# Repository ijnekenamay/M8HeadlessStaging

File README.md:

# M8 Headless Staging

This is a DIY project to push the [Dirtywave M8 Headless](https://github.com/Dirtywave/M8HeadlessFirmware) into a PCB and make it handheld.
Test build was done on the fabricated PCB. MIDI I/O AUDIO OUT seems to be working well.
Kicad data has been withheld from the public due to criticism that it would damage the market. Please contact.

## Now progress

- [x] Idea sketch
- [x] Draw proto Schematics
- [x] Design proto PCB
- [x] Proto type
- [x] Design PCB
- [x] Fabrication PCB
- [x] Test Build

## Latest Status

# Build

- It works almost perfectly, except for the audio input. I carefully researched Dirtywave's Discord, but could not
  figure it out. I gave up on it.
- Some wiring must be done by hand.
  This means that some wiring is not included on the PCB.
  For example, it is necessary to connect the key switch to the GPIO pins of the RSPi, and to connect the shutdown button to the GPIO pins.

## Parts list

- Raspberry Pi 3 Model B+(Raspberry Pi 4 Model B is better) \*1
- Teensy 4.1 \*1
- 90 deglee USB cable(You can find them at [Aliexpress](https://ja.aliexpress.com/item/10000315945874.html)) \*1
- Display for the Raspberry Pi (You can find them at [Aliexpress](https://aliexpress.com/item/4000380101537.html)) \*1
- PCM5102dac decorder (You can find them at [Aliexpress](https://aliexpress.com/item/1005002898278583.html)) \*1
- Kailh Low profile key switch with cap (You can find them at [Aliexpress](https://ja.aliexpress.com/item/32959996455.html)) \*8
- 3.7V Litium poly battery (You can find them at Aliexpress) \*1
- Ajustable battery module (You can find them at [Aliexpress](https://ja.aliexpress.com/item/4000087101515.html)) \*1
- Slide switch (2.54mm pich) \*1
- Tact switch (6mm*6mm) *1
- 30mm long hex spacer \*4
- 15mm long hex spacer \*4
- 6N138 optocoupler \*1
- other resistors and capacitor (STM assenbly use by JLCPCB)

## Setup Teensy

Be sure to follow the official manual.
The version you install must be 2.0.5. Otherwise, the midi i/o will not work.
https://github.com/DirtyWave/M8Docs/blob/main/docs/M8HeadlessSetup.md

## Setup Raspberry Pi

- Setup m8c
- Setup full screen
- Setup autostart
- Setup shutdown key(Use Tact switch)
- Setup key switches

### Setup m8c

The client software for Headless is [m8c](https://github.com/laamaa/m8c), which is published by laamaa.
The setup for using the m8c and Raspberry Pi can be seen in detail in the littlescale video.

### Setup full screen

You can set the fullscreen in the config in the m8c installation folder.

### Setup autostart

Put in a general autostart program.It's probably faster to ask Google than to ask me.
Then KICK The m8c startup command, ". /m8c".

### Setup shutdown key(Use Tact switch)

This one also plants a commonly used shutdown program. We connected the GND of the tact switch and the "shutdown button" pad on the PCB to GPIO5 (PIN29) and GND (PIN30) respectively.
This is because pins 1 to 28 are blocked by the display.
https://www2.quartoknows.com/page/raspberry-pi-shutdown-button

### Setup key switches

Key mapping is done using a program called "GPIONext", which is often used in RetroPi.
The GND must be connected to PIN39 or PIN34, but the other pins can be configured as you like. Use a wire to arrange the wires.
https://github.com/mholgatem/GPIOnext

The key layout to be set should follow the m8c manual.

Keys for controlling the progam:

- Up arrow = up
- Down arrow = down
- Left arrow = left
- Right arrow = right
- a / left shift = select
- s / space = start
- z / left alt = opt
- x / left ctrl = edit

## Other Parts

Other parts, such as the DAC module, simply need to be soldered as shown in the image to function.

## The following is a memorandum for development, but I leave it here just in case.

## Design Outline

- M8 Headless will be installed on teensy4.1.
- The client software for Headless is [m8c](https://github.com/laamaa/m8c), which is published by laamaa.
- The client computer will be a Raspberry Pi3 Model B+.
- For the display, we will use a third party display for the Raspberry Pi. (You can find them at [Aliexpress](https://aliexpress.com/item/4000380101537.html))
- We will implement MIDI IN & OUT.
- We will use the GPIO pins of the Raspberry pi to perform key emulation and try to get close to the original key layout.
- Sandwich the above various devices on two PCBs.
- If there is enough room, I would like to implement a battery module as well.

---

### Task1 Client and Display

---

The setup for using the m8c and Raspberry Pi can be seen in detail in the littlescale video.

Since this video shows video and audio output from the HDMI port, we will assume that audio output is available using a 3.5mm stereo jack if you use a touch display with audio output, available from [Aliexpress](https://aliexpress.com/item/4000380101537.html).
Or I'm thinking of getting the sound through a DAC module.

<blockquote class="twitter-tweet"><p lang="en" dir="ltr">hacked together a quick teensy 4.1 midi i/o and audio out board for making it a bit easier to use the <a href="https://twitter.com/hashtag/m8tracker?src=hash&amp;ref_src=twsrc%5Etfw">#m8tracker</a> headless version in my dawless setup <a href="https://t.co/O24RRRLSRL">pic.twitter.com/O24RRRLSRL</a></p>&mdash; Jonne Kokkonen (@laamaa) <a href="https://twitter.com/laamaa/status/1404158507188985856?ref_src=twsrc%5Etfw">June 13, 2021</a></blockquote>

## Practical notes

- Use Headless version 2.0.5, because MIDI I/O does not work well.

---

### Task2 MIDI IN&OUT

---

As has been discussed several times on Dirtywave's Discord, it seems possible to implement MIDI IN and OUT in a Headless environment.
The developer, trash80, commented "MIDI in is pin 28, MIDI out is pin 1, it's enabled".
I plan to implement them as shown in the schematic below.

---

### Task3 Key Switch

---

Key emulation (key mapping) using the GPIO pins of the Raspberry Pi is also currently in the hypothetical stage.
There are plenty of people practicing something similar with the Retropi!
For the keyswitch itself, I will use the same one as the M8 original.

---

### Task4 Battery Module

---

I'd like to use the tiny little battery charging modules that [Aliexpress](https://ja.aliexpress.com/item/4001196670805.html) sells so that I can seamlessly connect the power supply, PSU, and charging.
I think I will agonize over where to put the batteries!

---

### Reference data

---

James' work has addressed some of the concerns of this project!

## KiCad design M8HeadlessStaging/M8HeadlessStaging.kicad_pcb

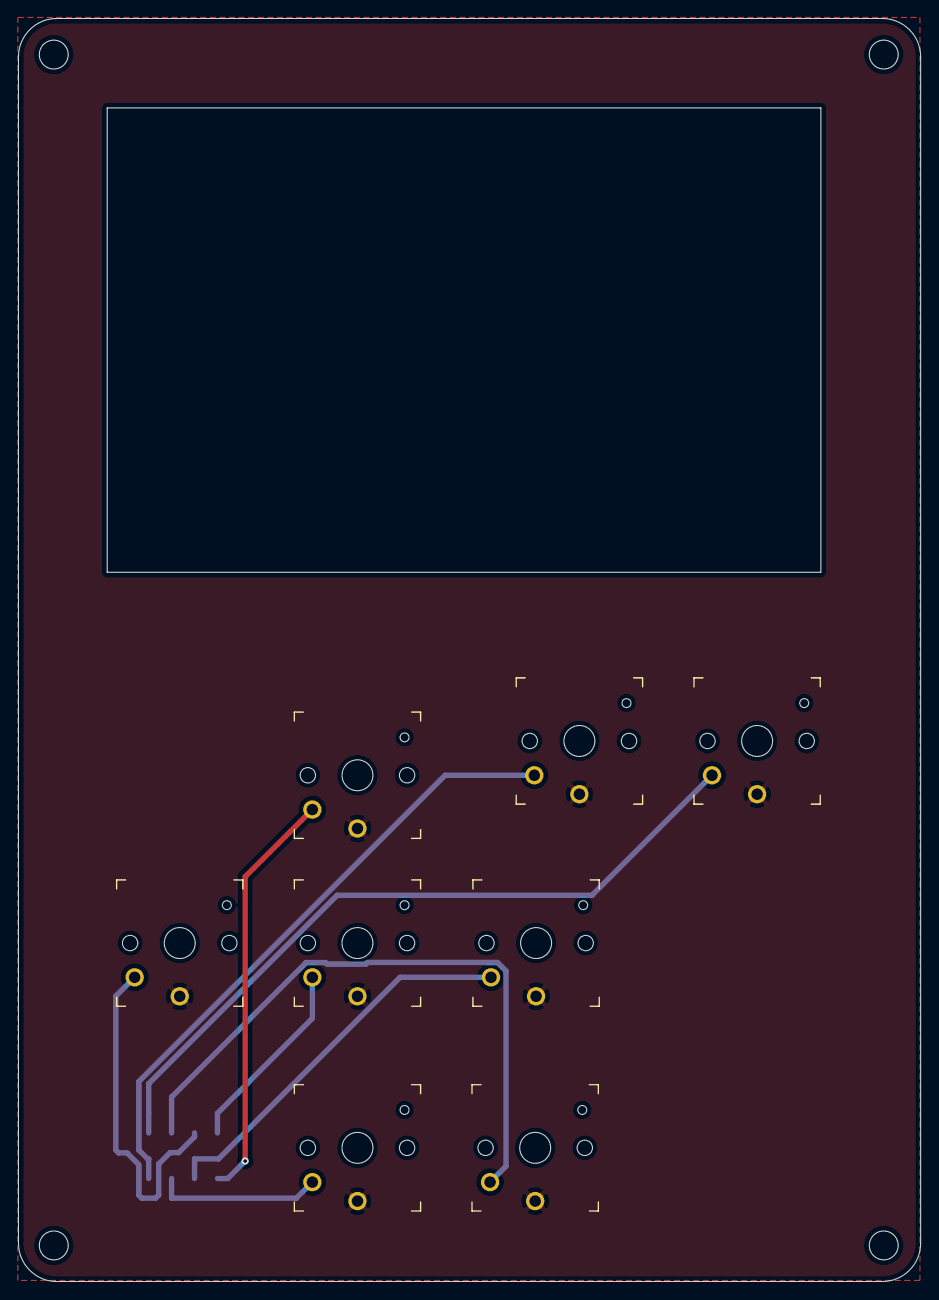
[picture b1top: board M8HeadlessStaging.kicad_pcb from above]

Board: 2 copper layers, 100.0 x 140.0 mm, 9 parts (1 on the bottom side), 9 nets.

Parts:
J3: Key_frontpanel; PinHeader_2x05_P2.54mm_Vertical_SMD
SW1: UP; SW_PG1350
SW2: DOWN; SW_PG1350
SW3: RIGHT; SW_PG1350
SW4: LEFT; SW_PG1350
SW5: SHIFT; SW_PG1350
SW6: PLAY; SW_PG1350
SW7: OPTION; SW_PG1350
SW8: EDIT; SW_PG1350

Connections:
DOWN: J3.2, SW2.2
EDIT: J3.8, SW8.2
GND: J3.9, J3.10, SW1.1, SW2.1, SW3.1, SW4.1, SW5.1, SW6.1, SW7.1, SW8.1
LEFT: J3.4, SW4.2
OPTION: J3.7, SW7.2
PLAY: J3.6, SW6.2
RIGHT: J3.3, SW3.2
SHIFT: J3.5, SW5.2
UP: J3.1, SW1.2

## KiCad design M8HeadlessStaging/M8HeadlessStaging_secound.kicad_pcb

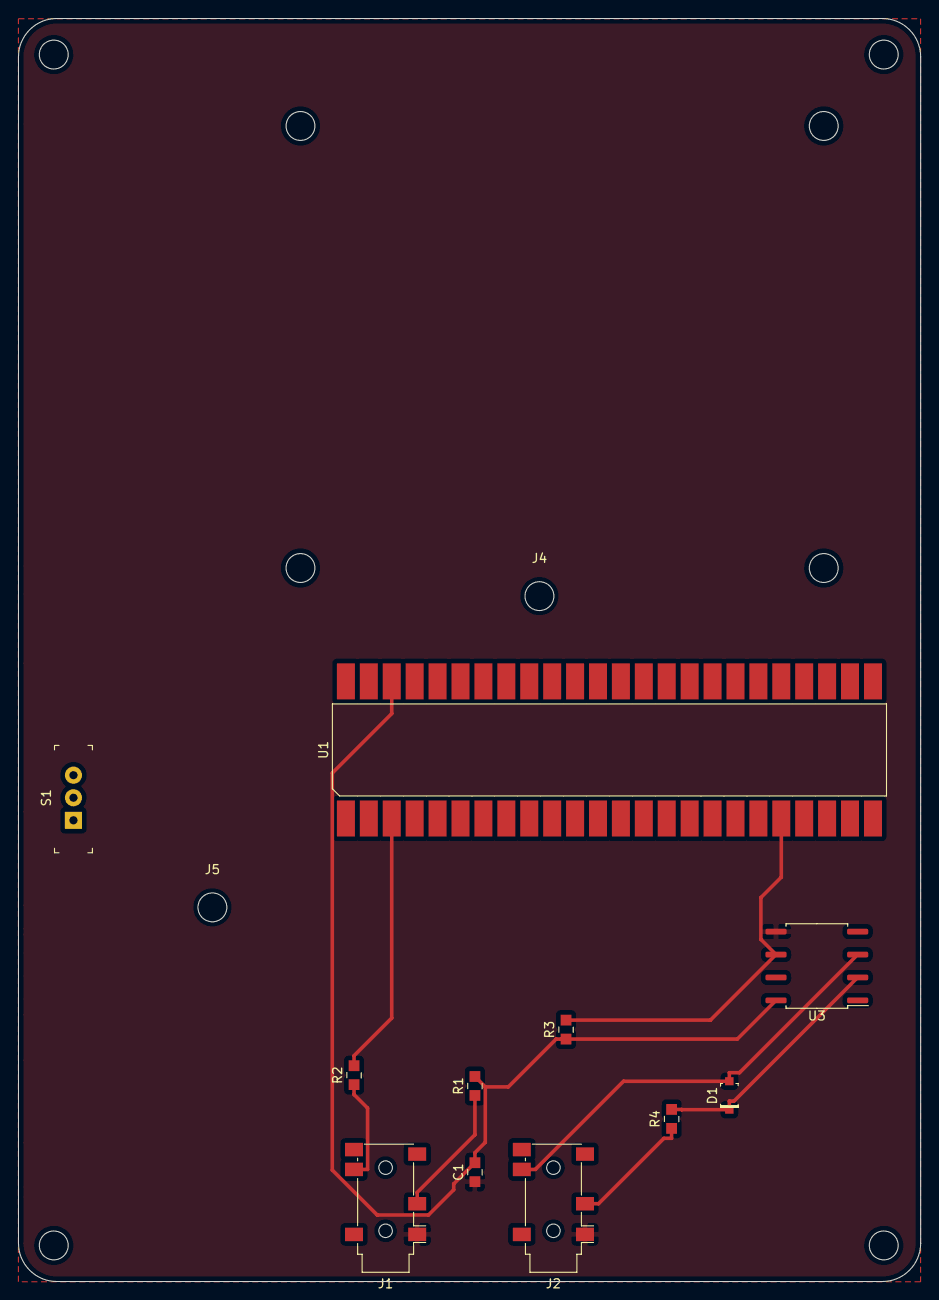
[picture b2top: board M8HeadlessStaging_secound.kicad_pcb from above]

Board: 2 copper layers, 100.0 x 140.0 mm, 13 parts (0 on the bottom side), 11 nets.

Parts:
C1: 0.1uF; 0805
D1: 1n4148; SOD-123
J1: MIDI OUT; Jack_3.5mm_PJ311_Horizontal
J2: MIDI IN; Jack_3.5mm_PJ311_Horizontal
J4: TO_RASP_VIN; MountingHole_3.2mm_M3
J5: TO_BAT_MODULE; MountingHole_3.2mm_M3
R1, R2: 47R; 0805
R3: 470R; 0805
R4: 220R; 0805
S1: SLIDE_SWITCH; Switch_Slide_11.6x4mm_EG1218
U1: Teensy4.1; TEENSY4.1
U3: 6N138; SOP-8_6.62x9.15mm_P2.54mm

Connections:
+3V3: C1.2, R1.2, R3.1, U1.46, U3.8
GND: C1.1, J1.1, J2.1, U3.5
unnamed: D1.K, R4.2, U3.2
unnamed: D1.A, J2.4, U3.3
unnamed: J1.3, R1.1
unnamed: J1.4, R2.1
unnamed: J2.3, R4.1
unnamed: J4.1, S1.2
unnamed: J5.1, S1.1
RX1: R3.2, U1.20, U3.6
TX1: R2.2, U1.3

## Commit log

2021-11-04 Add README
2021-11-04 Add schematic
2021-11-04 add schematics
2021-11-05 add image
2021-11-12 Add PCB
2021-12-14 addTestbuild
